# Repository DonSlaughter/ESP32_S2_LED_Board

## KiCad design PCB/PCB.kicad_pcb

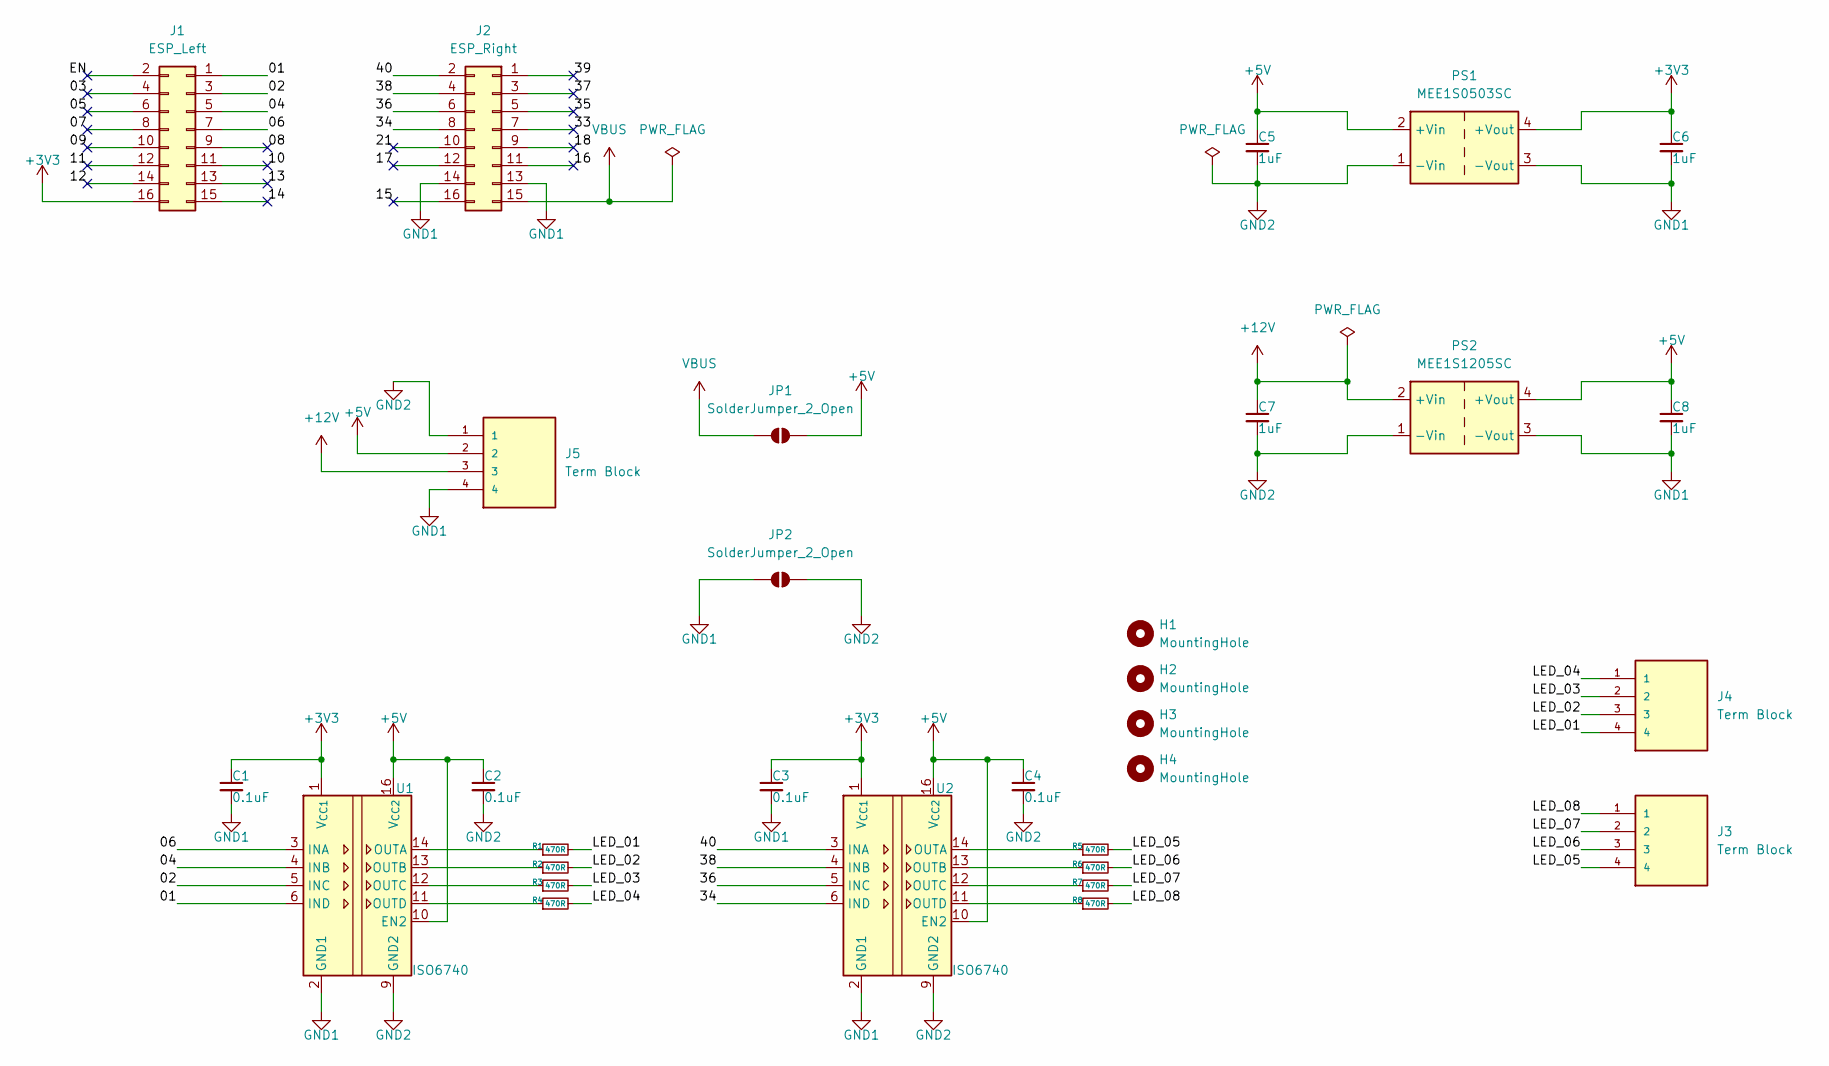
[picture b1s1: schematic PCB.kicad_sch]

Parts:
C1, C2, C3, C4: 0.1uF; C_0603_1608Metric; Part Nr. CL10B104KB8NNNC
C5, C6, C7, C8: 1uF; C_0603_1608Metric; Part Nr. CL10A105KB8NNNC
H1, H2, H3, H4: MountingHole; MountingHole_4.3mm_M4
J1: ESP_Left; PinSocket_2x08_P2.54mm_Vertical
J2: ESP_Right; PinSocket_2x08_P2.54mm_Vertical
J3, J4, J5: Term Block; TE_1985218; PARTREV 29.03.2021
JP1, JP2: SolderJumper_2_Open; SolderJumper-2_P1.3mm_Open_RoundedPad1.0x1.5mm
PS1: MEE1S0503SC; Converter_DCDC_Murata_MEE1SxxxxSC_THT
PS2: MEE1S1205SC; Converter_DCDC_Murata_MEE1SxxxxSC_THT
R1, R2, R3, R4, R5, R6, R7, R8: 470R; R_0603_1608Metric; Part Nr. RC0603JR-07470RL
U1, U2: ISO6740; SOIC-16W_7.5x10.3mm_P1.27mm; Part Nr. ISO6740FDWR

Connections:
+3V3: C1.1, C3.1, C6.1, J1.16, PS1.4 (+Vout), U1.1 (V_{CC1}), U2.1 (V_{CC1})
+5V: C2.1, C4.1, C5.1, C8.1, J5.2, JP1.2 (B), PS1.2 (+Vin), PS2.4 (+Vout), U1.10 (EN2), U1.16 (V_{CC2}), U2.10 (EN2), U2.16 (V_{CC2})
+12V: C7.1, J5.3, PS2.2 (+Vin)
/01: J1.1, U1.6 (IND)
/02: J1.3, U1.5 (INC)
/03: J1.4
/04: J1.5, U1.4 (INB)
/05: J1.6
/06: J1.7, U1.3 (INA)
/07: J1.8
/08: J1.9
/09: J1.10
/10: J1.11
/11: J1.12
/12: J1.14
/13: J1.13
/14: J1.15
/15: J2.16
/16: J2.11
/17: J2.12
/18: J2.9
/21: J2.10
/33: J2.7
/34: J2.8, U2.6 (IND)
/35: J2.5
/36: J2.6, U2.5 (INC)
/37: J2.3
/38: J2.4, U2.4 (INB)
/39: J2.1
/40: J2.2, U2.3 (INA)
/EN: J1.2
/LED_01: J4.4, R1.2
/LED_02: J4.3, R2.2
/LED_03: J4.2, R3.2
/LED_04: J4.1, R4.2
/LED_05: J3.4, R5.2
/LED_06: J3.3, R6.2
/LED_07: J3.2, R7.2
/LED_08: J3.1, R8.2
GND1: C1.2, C3.2, C6.2, C8.2, J2.13, J2.14, J5.4, JP2.1 (A), PS1.3 (-Vout), PS2.3 (-Vout), U1.2 (GND1), U1.8 (GND1), U2.2 (GND1), U2.8 (GND1)
GND2: C2.2, C4.2, C5.2, C7.2, J5.1, JP2.2 (B), PS1.1 (-Vin), PS2.1 (-Vin), U1.9 (GND2), U1.15 (GND2), U2.9 (GND2), U2.15 (GND2)
unnamed: R1.1, U1.14 (OUTA)
unnamed: R2.1, U1.13 (OUTB)
unnamed: R3.1, U1.12 (OUTC)
unnamed: R4.1, U1.11 (OUTD)
unnamed: R5.1, U2.14 (OUTA)
unnamed: R6.1, U2.13 (OUTB)
unnamed: R7.1, U2.12 (OUTC)
unnamed: R8.1, U2.11 (OUTD)
VBUS: J2.15, JP1.1 (A)

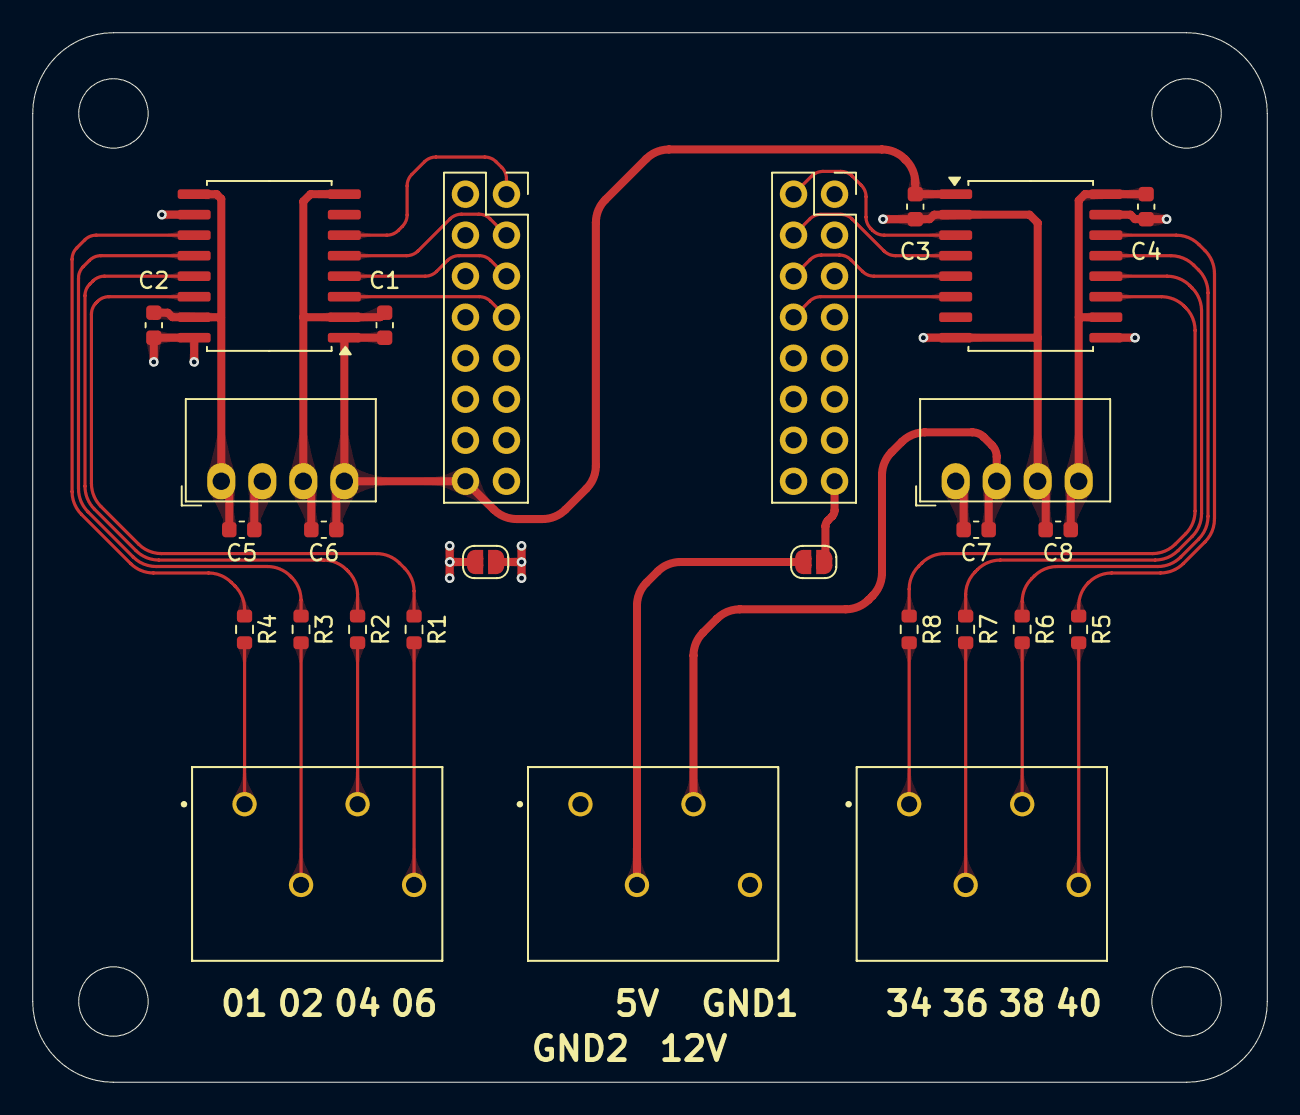
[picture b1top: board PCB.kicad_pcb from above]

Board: 4 copper layers, 76.5 x 65.0 mm, 31 parts (0 on the bottom side), 30 nets.

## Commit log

2025-02-07 backups removed
2025-02-11 first test with case
2025-02-11 gerber files for production and assembly files for 3d printing added
2025-02-12 test assembly
2025-02-17 new assembly
2025-02-18 new approach
